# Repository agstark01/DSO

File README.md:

# DSO
Making a digital oscilloscope for frequency range upto 500khz and voltage range upto +-10V. Sharing the waveforms via pc communication to project it on gui using USB2.0 1MBps speed
## You can see full schematics in [DSO_1draft.pdf](assessment1/DSO_1draft/DSO_1draft.pdf).

## Hardware Subsystems & Circuit Schematics

### 1. Analog Input & Channel Multiplexing
Routes and selects between analog input channels and attenuation paths to direct the conditioned signal toward the sampling stage.

---

### 2. Anti-Aliasing Filter
An active low-pass filter stage designed to attenuate high-frequency components above the Nyquist limit, preventing aliasing distortion at the ADC inputs.

---

### 3. PWM-to-DC Offset Generator
Filters a high-frequency PWM signal from the microcontroller through a low-pass network, producing an adjustable analog DC offset to center and bias bipolar input waveforms within the ADC's 0–3.3V dynamic range.

---

### 4. Symmetric Dual Supply Generation (±5V)
Generates clean positive (this stage is updated please see pdf) (+5V) and negative (-5V) rails to supply the operational amplifiers, providing the necessary headroom and swing for true bipolar signal conditioning.

---

### 5. Onboard Function Generator
Generates test signals (e.g., standard 1 kHz square reference or calibration waveforms) for probe compensation, debugging, and self-testing.

---

### 6. Input Connectors & Channels
Interface connectors (BNC/header pins) for Channel 1 and Channel 2, providing signal entry, grounding, and initial protection.

---

### 7. MCU Programming & Debug Header
Breakout interface (SWD/JTAG and UART/power pins) for flashing firmware to the microcontroller and monitoring real-time telemetry during development.

---

### 8. Net Name & Pin Matching Guide
Reference diagram mapping schematic netlabels, board bus connections, and microcontroller GPIO pinouts across different modules.

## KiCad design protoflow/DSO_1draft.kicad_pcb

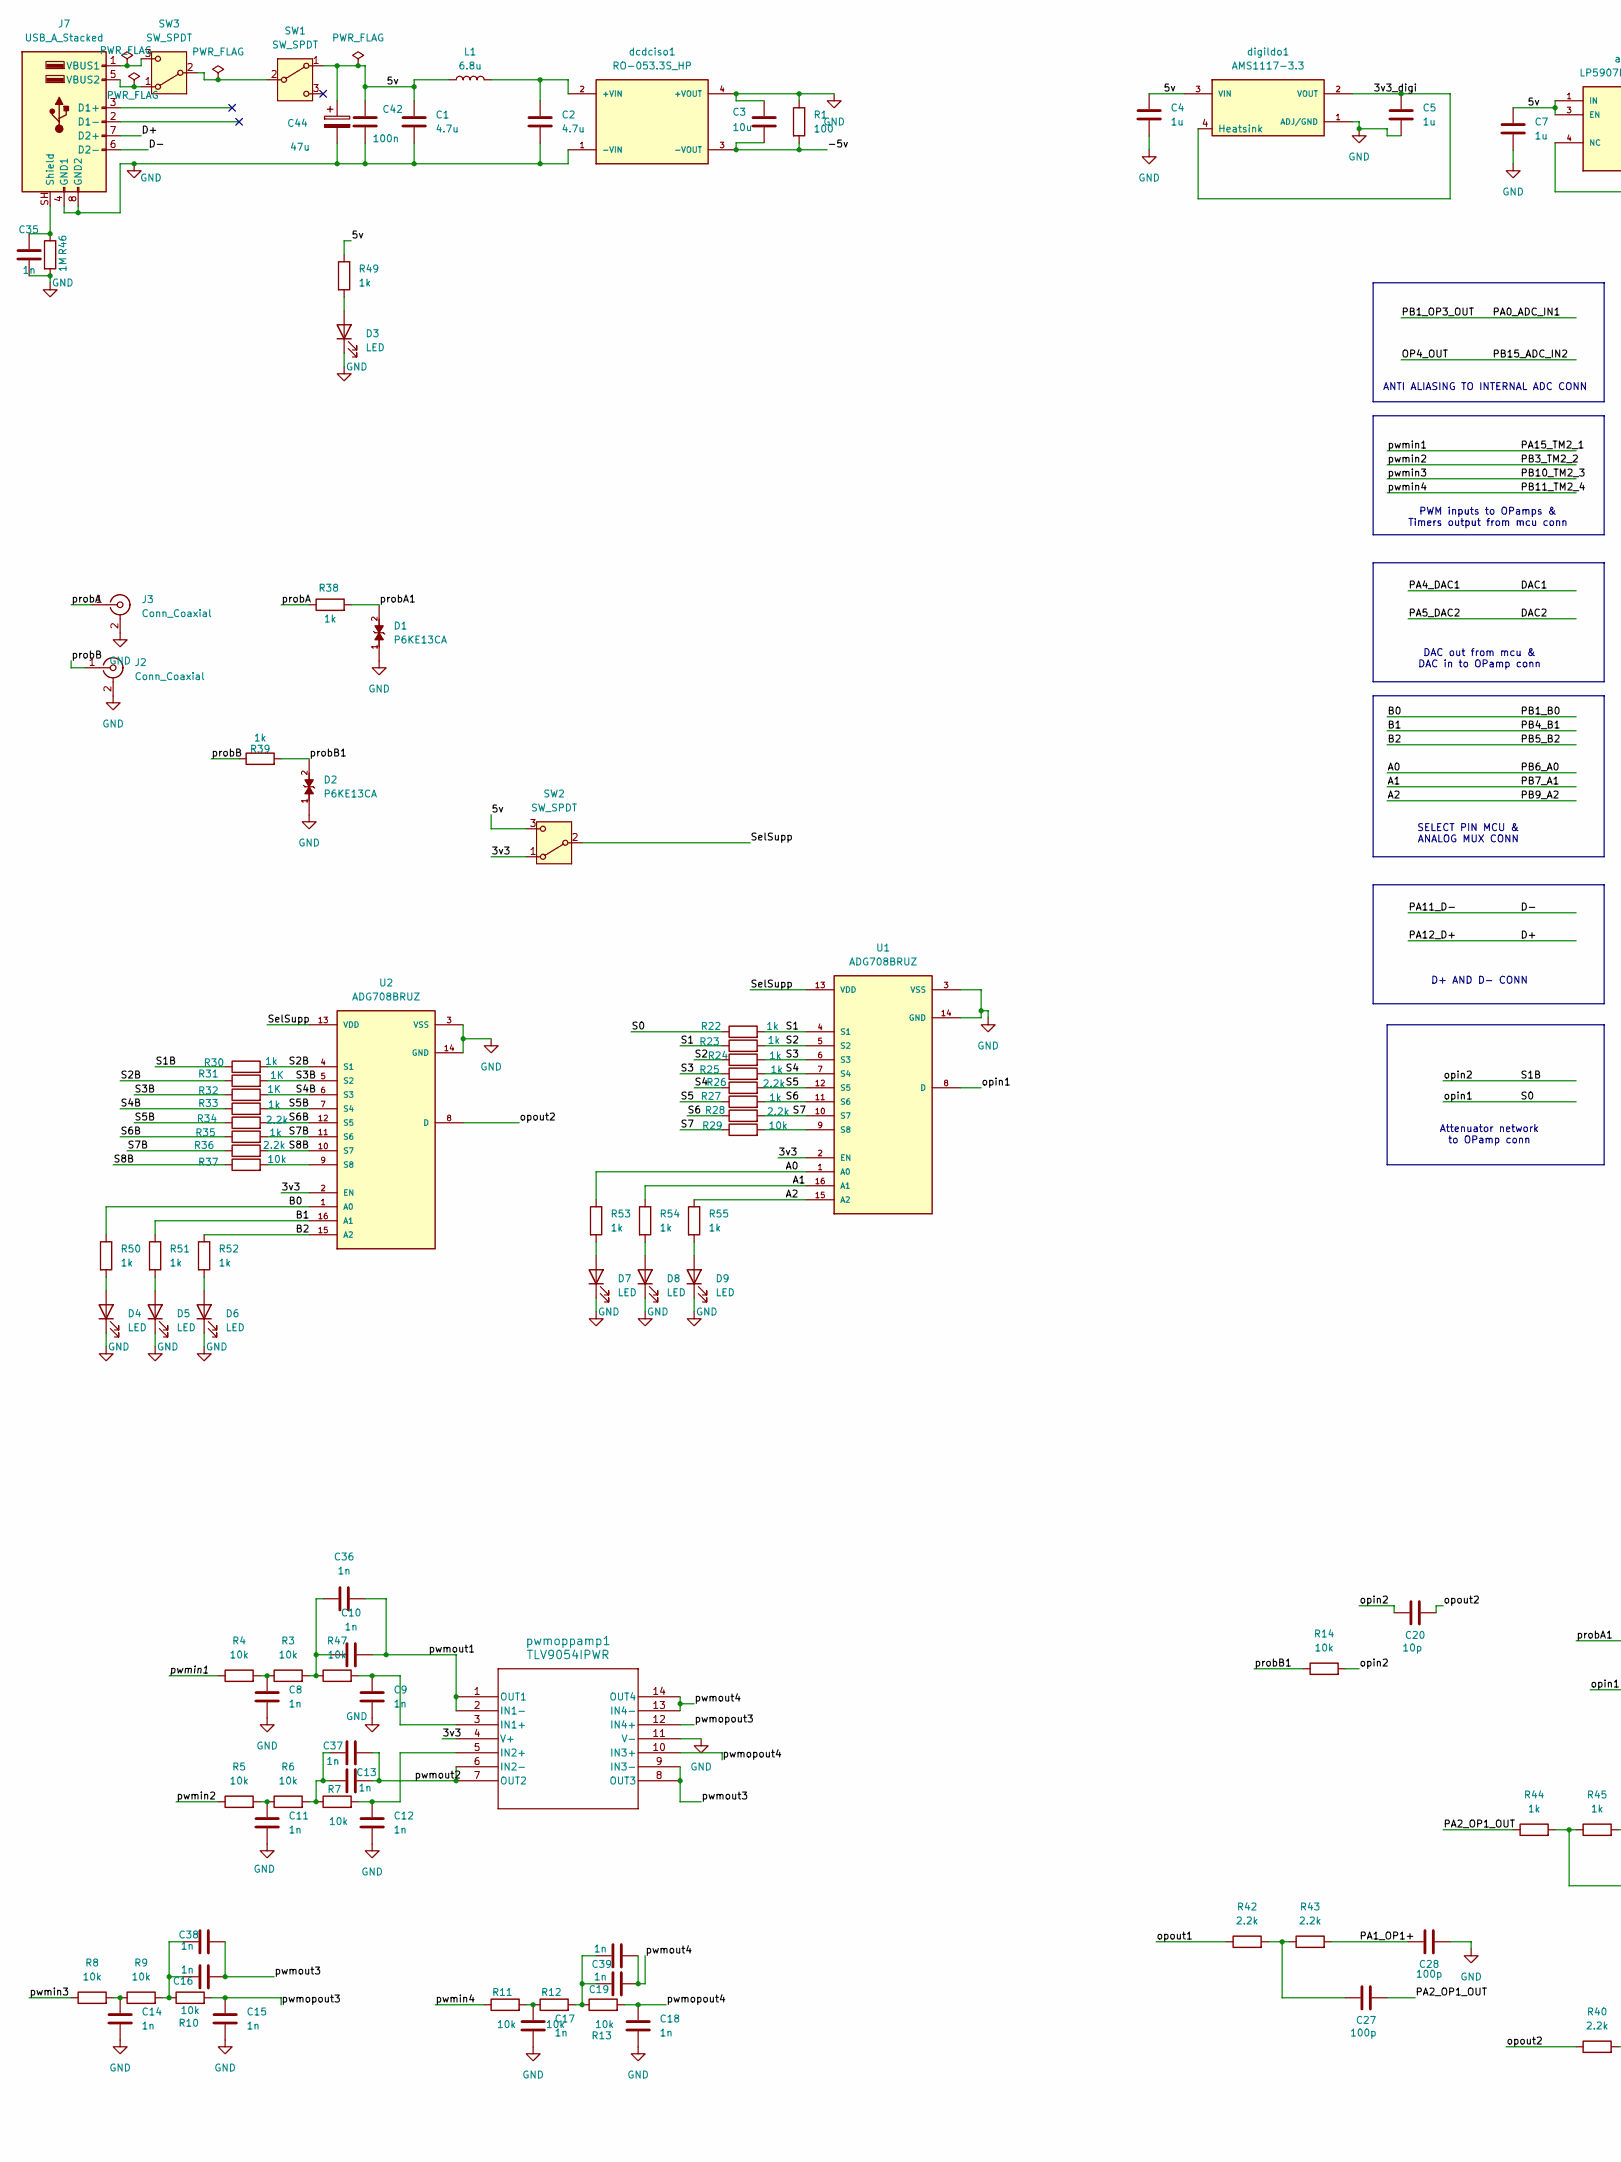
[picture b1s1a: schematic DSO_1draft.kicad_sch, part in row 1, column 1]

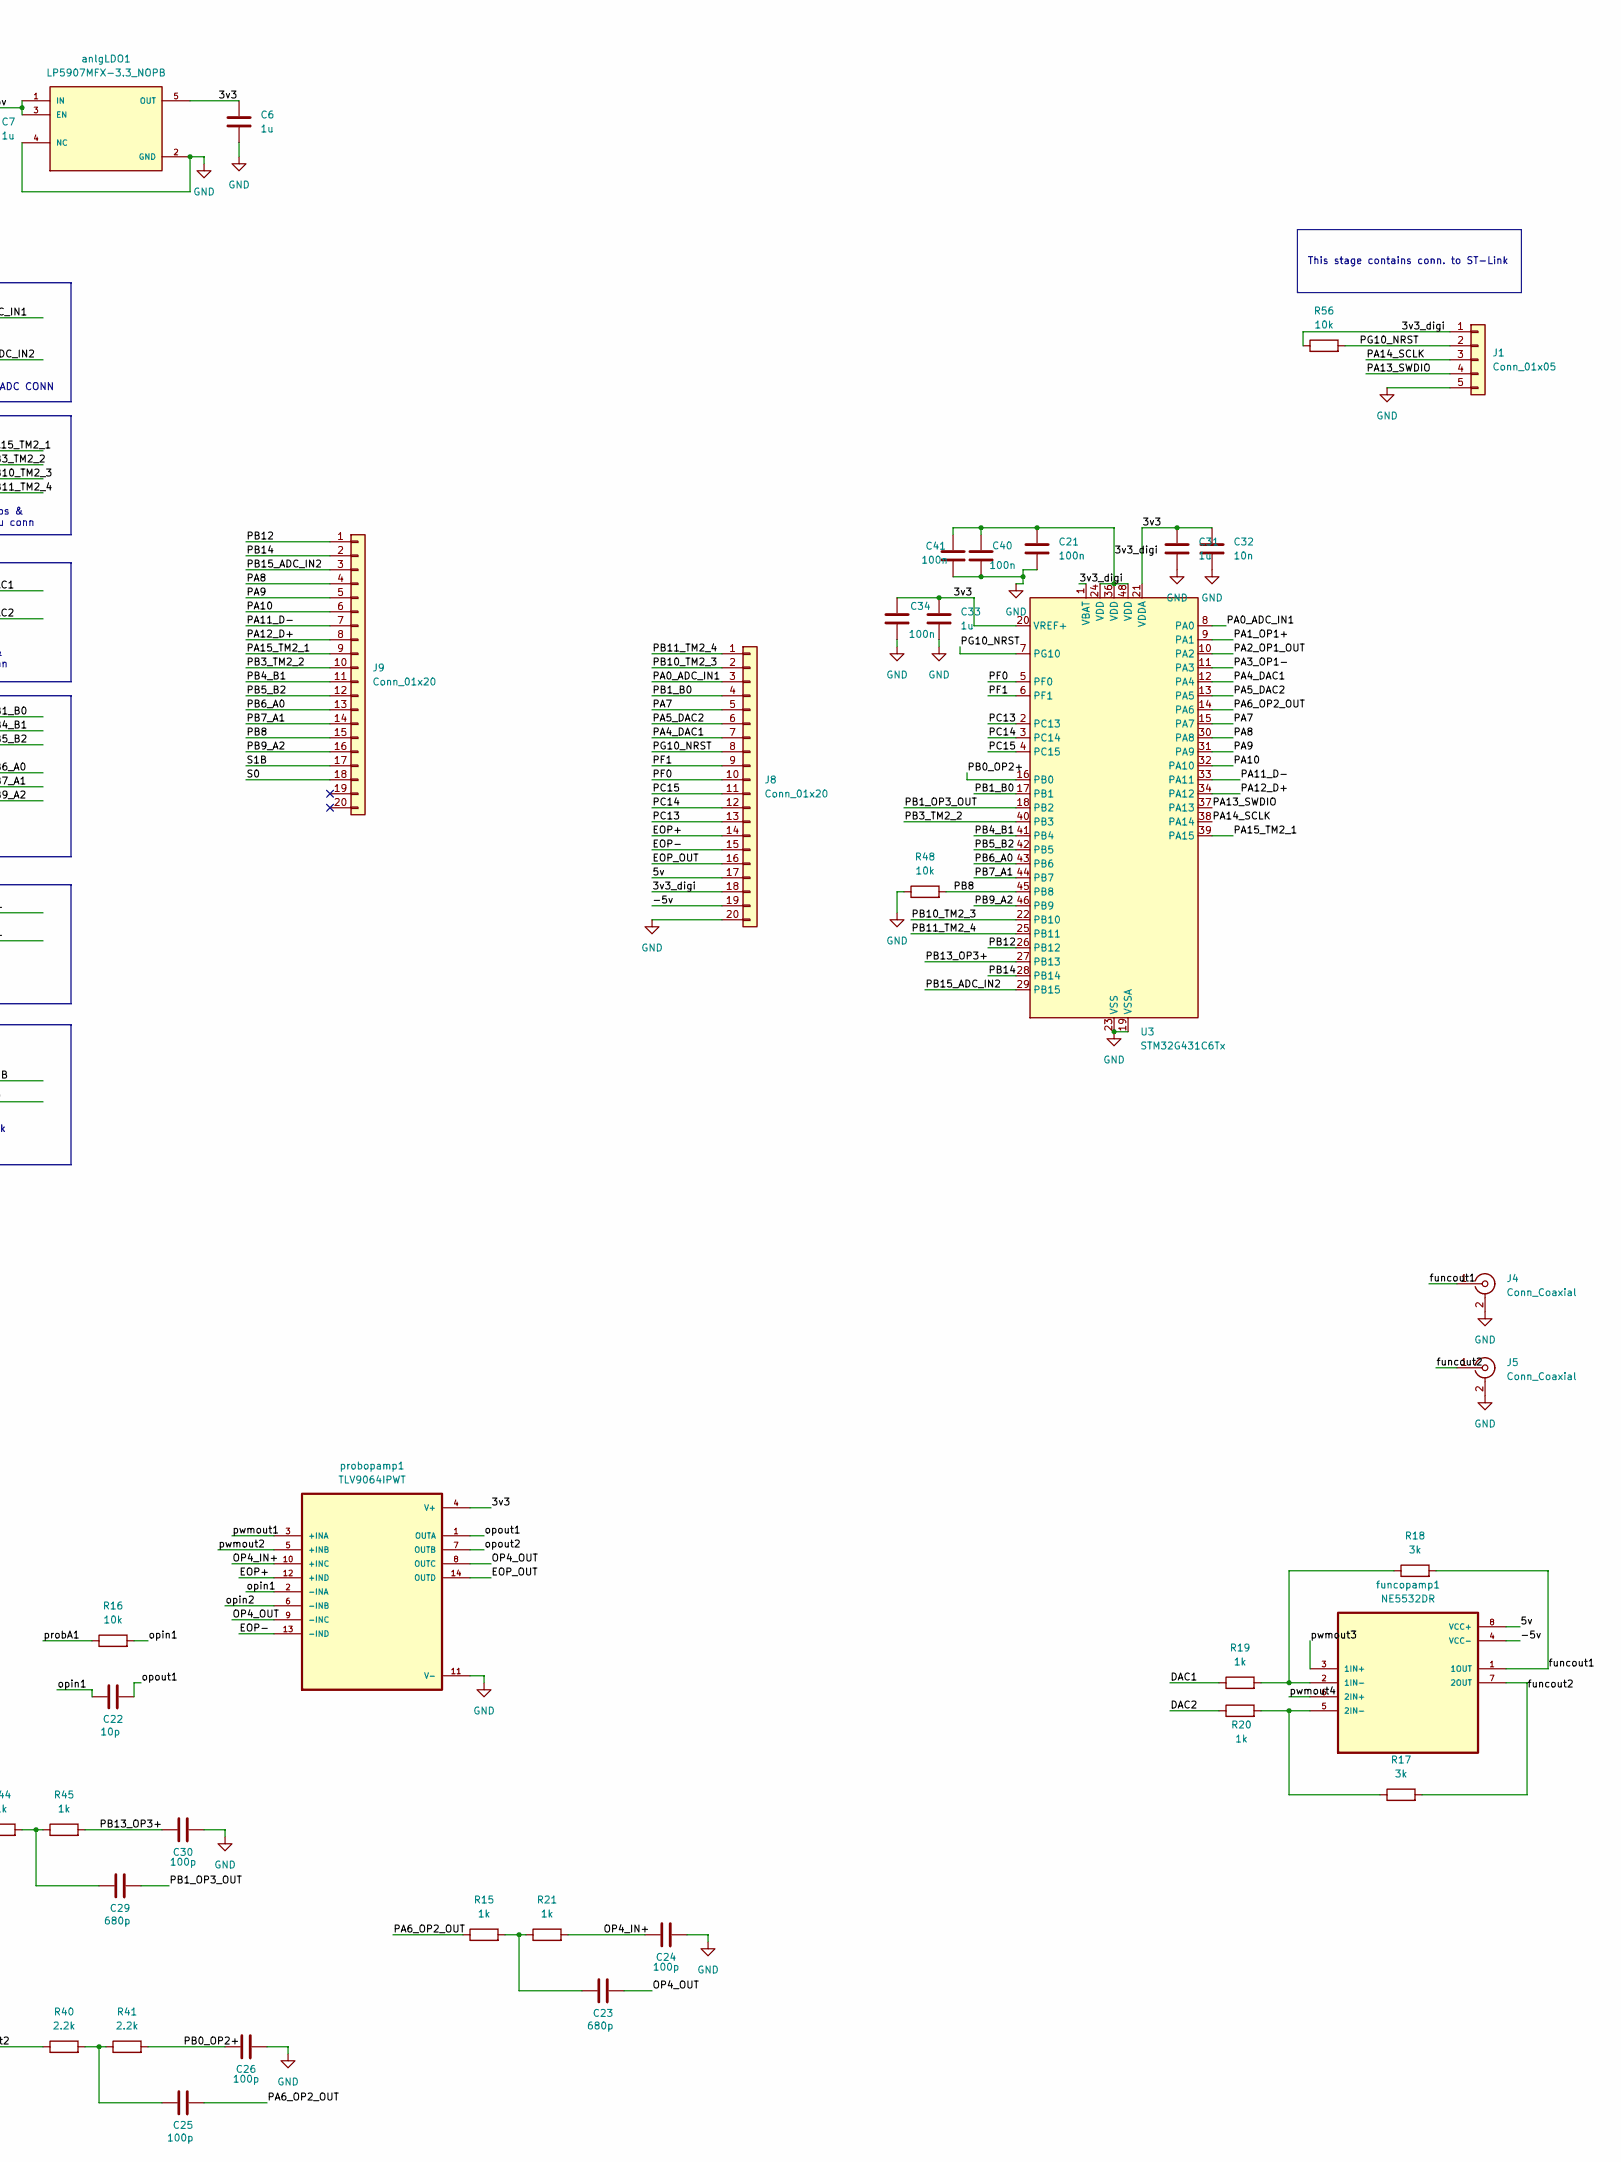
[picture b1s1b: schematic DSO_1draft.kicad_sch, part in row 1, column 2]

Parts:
C1, C2: 4.7u; C_1206_3216Metric_Pad1.33x1.80mm_HandSolder
C3: 10u; C_1206_3216Metric_Pad1.33x1.80mm_HandSolder
C4, C5, C6, C7, C31, C33: 1u; C_1206_3216Metric_Pad1.33x1.80mm_HandSolder
C8, C9, C10, C11, C12, C13, C14, C15, C16, C17, C18, C19, C35, C36, C37, C38, C39: 1n; C_1206_3216Metric_Pad1.33x1.80mm_HandSolder
C20, C22: 10p; C_1206_3216Metric_Pad1.33x1.80mm_HandSolder
C21, C34, C40, C41, C42: 100n; C_1206_3216Metric_Pad1.33x1.80mm_HandSolder
C23, C29: 680p; C_1206_3216Metric_Pad1.33x1.80mm_HandSolder
C24, C25, C26, C27, C28, C30: 100p; C_1206_3216Metric_Pad1.33x1.80mm_HandSolder
C32: 10n; C_1206_3216Metric_Pad1.33x1.80mm_HandSolder
C44: 47u; C_Radial_D5.0mm_H11.0mm_P2.00mm
D1, D2: P6KE13CA; DIOAD1300W80L670D310; PARTREV O2109
D3, D4, D5, D6, D7, D8, D9: LED; LED_1206_3216Metric
J1: Conn_01x05; PinHeader_1x05_P2.54mm_Vertical
J2, J3, J4, J5: Conn_Coaxial; BNC_Amphenol_B6252HB-NPP3G-50_Horizontal
J7: USB_A_Stacked; USB_A_CUI_UJ2-ADH-TH_Horizontal_Stacked
J8, J9: Conn_01x20; PinHeader_2x10_P2.54mm_Vertical
L1: 6.8u; L_Axial_L11.0mm_D4.5mm_P15.24mm_Horizontal_Fastron_MECC
R1: 100; R_Axial_DIN0207_L6.3mm_D2.5mm_P7.62mm_Horizontal
R3, R4, R5, R6, R7, R8, R9, R10, R11, R12, R13, R14, R16, R29, R37, R47, R48, R56: 10k; R_1206_3216Metric_Pad1.30x1.75mm_HandSolder
R15, R19, R20, R21, R22, R23, R24, R25, R27, R30, R33, R35, R38, R39, R44, R45, R49, R50, R51, R52, R53, R54, R55: 1k; R_1206_3216Metric_Pad1.30x1.75mm_HandSolder
R17, R18: 3k; R_1206_3216Metric_Pad1.30x1.75mm_HandSolder
R26, R28, R34, R36, R40, R41, R42, R43: 2.2k; R_1206_3216Metric_Pad1.30x1.75mm_HandSolder
R31, R32: 1K; R_1206_3216Metric_Pad1.30x1.75mm_HandSolder
R46: 1M; R_Axial_DIN0207_L6.3mm_D2.5mm_P7.62mm_Horizontal
SW1, SW2, SW3: SW_SPDT; SS-12F17_1P2T
U1, U2: ADG708BRUZ; TSSOP16
U3: STM32G431C6Tx; LQFP-48_7x7mm_P0.5mm
anlgLDO1: LP5907MFX-3.3_NOPB; SOT95P280X145-5N; PARTREV Q
dcdciso1: RO-053.3S_HP; CONV_RO-053.3S_HP; PARTREV 3
digildo1: AMS1117-3.3; SOT229P700X180-4N; PARTREV NA
funcopamp1: NE5532DR; SOIC127P599X175-8N
probopamp1: TLV9064IPWT; SOP65P640X120-14N
pwmoppamp1: TLV9054IPWR; U_TSSOP_PW_TEX-M

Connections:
/3v3: C6.1, C31.1, C32.1, C33.1, C34.1, SW2.1 (A), U1.2 (EN), U2.2 (EN), U3.20 (VREF+), U3.21 (VDDA), anlgLDO1.5 (OUT), probopamp1.4 (V+), pwmoppamp1.4 (V+)
/3v3_digi: C5.1, C21.1, C40.1, C41.1, J1.1, J8.18, R56.1, U3.1 (VBAT), U3.24 (VDD), U3.36 (VDD), U3.48 (VDD), digildo1.2 (VOUT), digildo1.4 (Heatsink)
/5v: C1.1, C4.1, C7.1, C42.1, C44.1, J8.17, L1.1, R49.1, SW1.1 (A), SW2.3 (C), anlgLDO1.1 (IN), anlgLDO1.3 (EN), digildo1.3 (VIN), funcopamp1.8 (VCC+)
/-5v: C3.2, J8.19, R1.2, dcdciso1.3 (-VOUT), funcopamp1.4 (VCC-)
/A0: J9.13, R53.1, U1.1 (A0), U3.43 (PB6)
/A1: J9.14, R54.1, U1.16 (A1), U3.44 (PB7)
/A2: J9.16, R55.1, U1.15 (A2), U3.46 (PB9)
/B0: J8.4, R50.1, U2.1 (A0), U3.17 (PB1)
/B1: J9.11, R51.1, U2.16 (A1), U3.41 (PB4)
/B2: J9.12, R52.1, U2.15 (A2), U3.42 (PB5)
/D+: J7.7 (D2+), J9.8, U3.34 (PA12)
/D-: J7.6 (D2-), J9.7, U3.33 (PA11)
/DAC1: J8.7, R19.1, U3.12 (PA4)
/DAC2: J8.6, R20.1, U3.13 (PA5)
/EOP+: J8.14, probopamp1.12 (+IND)
/EOP-: J8.15, probopamp1.13 (-IND)
/EOP_OUT: J8.16, probopamp1.14 (OUTD)
/OP4_IN+: C24.1, R21.2, probopamp1.10 (+INC)
/OP4_OUT: C23.2, J9.3, U3.29 (PB15), probopamp1.8 (OUTC), probopamp1.9 (-INC)
/PA0_ADC_IN1: C29.2, J8.3, U3.8 (PA0), U3.18 (PB2)
/PA1_OP1+: C28.1, R43.2, U3.9 (PA1)
/PA2_OP1_OUT: C27.2, R44.1, U3.10 (PA2)
/PA3_OP1-: U3.11 (PA3)
/PA6_OP2_OUT: C25.2, R15.1, U3.14 (PA6)
/PA7: J8.5, U3.15 (PA7)
/PA8: J9.4, U3.30 (PA8)
/PA9: J9.5, U3.31 (PA9)
/PA10: J9.6, U3.32 (PA10)
/PA13_SWDIO: J1.4, U3.37 (PA13)
/PA14_SCLK: J1.3, U3.38 (PA14)
/PA15_TM2_1: J9.9, R4.1, U3.39 (PA15)
/PB0_OP2+: C26.1, R41.2, U3.16 (PB0)
/PB3_TM2_2: J9.10, R5.1, U3.40 (PB3)
/PB8: J9.15, R48.2, U3.45 (PB8)
/PB10_TM2_3: J8.2, R8.1, U3.22 (PB10)
/PB11_TM2_4: J8.1, R11.1, U3.25 (PB11)
/PB12: J9.1, U3.26 (PB12)
/PB13_OP3+: C30.1, R45.2, U3.27 (PB13)
/PB14: J9.2, U3.28 (PB14)
/PC13: J8.13, U3.2 (PC13)
/PC14: J8.12, U3.3 (PC14)
/PC15: J8.11, U3.4 (PC15)
/PF0: J8.10, U3.5 (PF0)
/PF1: J8.9, U3.6 (PF1)
/PG10_NRST: J1.2, J8.8, R56.2, U3.7 (PG10)
/S0: C22.1, J9.18, R16.2, R22.1, U1.8 (D), probopamp1.2 (-INA)
/S1: R22.2, R23.1, U1.4 (S1)
/S1B: C20.1, J9.17, R14.2, R30.1, probopamp1.6 (-INB)
/S2: R23.2, R24.1, U1.5 (S2)
/S2B: R30.2, R31.1, U2.4 (S1)
/S3: R24.2, R25.1, U1.6 (S3)
/S3B: R31.2, R32.1, U2.5 (S2)
/S4: R25.2, R26.1, U1.7 (S4)
/S4B: R32.2, R33.1, U2.6 (S3)
/S5: R26.2, R27.1, U1.12 (S5)
/S5B: R33.2, R34.1, U2.7 (S4)
/S6: R27.2, R28.1, U1.11 (S6)
/S6B: R34.2, R35.1, U2.12 (S5)
/S7: R28.2, R29.1, U1.10 (S7)
/S7B: R35.2, R36.1, U2.11 (S6)
/S8B: R36.2, R37.1, U2.10 (S7)
/SelSupp: SW2.2 (B), U1.13 (VDD), U2.13 (VDD)
/funcout1: J4.1 (In), R18.2, funcopamp1.1 (1OUT)
/funcout2: J5.1 (In), R17.2, funcopamp1.7 (2OUT)
/opout1: C22.2, R42.1, probopamp1.1 (OUTA)
/opout2: C20.2, R40.1, U2.8 (D), probopamp1.7 (OUTB)
/probA: J3.1 (In), R38.1
/probA1: D1.2, R16.1, R38.2
/probB: J2.1 (In), R39.1
/probB1: D2.2, R14.1, R39.2
/pwmopout3: C15.1, R10.2, pwmoppamp1.12 (IN4+)
/pwmopout4: C18.1, R13.2, pwmoppamp1.10 (IN3+)
/pwmout1: C10.2, C36.2, probopamp1.3 (+INA), pwmoppamp1.1 (OUT1), pwmoppamp1.2 (IN1-)
/pwmout2: C13.2, C37.2, probopamp1.5 (+INB), pwmoppamp1.6 (IN2-), pwmoppamp1.7 (OUT2)
/pwmout3: C16.2, C38.2, funcopamp1.3 (1IN+), pwmoppamp1.8 (OUT3), pwmoppamp1.9 (IN3-)
/pwmout4: C19.2, C39.2, funcopamp1.6 (2IN+), pwmoppamp1.13 (IN4-), pwmoppamp1.14 (OUT4)
GND: C1.2, C2.2, C3.1, C4.2, C5.2, C6.2, C7.2, C8.2, C9.2, C11.2, C12.2, C14.2, C15.2, C17.2, C18.2, C21.2, C24.2, C26.2, C28.2, C30.2, C31.2, C32.2, C33.2, C34.2, C35.2, C40.2, C41.2, C42.2, C44.2, D1.1, D2.1, D3.1 (K), D4.1 (K), D5.1 (K), D6.1 (K), D7.1 (K), D8.1 (K), D9.1 (K), J1.5, J2.2 (Ext), J3.2 (Ext), J4.2 (Ext), J5.2 (Ext), J7.4 (GND1), J7.8 (GND2), J8.20, R1.1, R46.2, R48.1, U1.3 (VSS), U1.14 (GND), U2.3 (VSS), U2.14 (GND), U3.19 (VSSA), U3.23 (VSS), U3.35 (VSS), U3.47 (VSS), anlgLDO1.2 (GND), anlgLDO1.4 (NC), dcdciso1.1 (-VIN), dcdciso1.4 (+VOUT), digildo1.1 (ADJ/GND), probopamp1.11 (V-), pwmoppamp1.11 (V-)
unnamed: C8.1, R3.1, R4.2
unnamed: C10.1, C36.1, R3.2, R47.1
unnamed: C11.1, R5.2, R6.1
unnamed: C13.1, C37.1, R6.2, R7.1
unnamed: C14.1, R8.2, R9.1
unnamed: C16.1, C38.1, R9.2, R10.1
unnamed: C17.1, R11.2, R12.1
unnamed: C19.1, C39.1, R12.2, R13.1
unnamed: C23.1, R15.2, R21.1
unnamed: C25.1, R40.2, R41.1
unnamed: C27.1, R42.2, R43.1
unnamed: C29.1, R44.2, R45.1
unnamed: D3.2 (A), R49.2
unnamed: D4.2 (A), R50.2
unnamed: D5.2 (A), R51.2
unnamed: D6.2 (A), R52.2
unnamed: D7.2 (A), R53.2
unnamed: D8.2 (A), R54.2
unnamed: D9.2 (A), R55.2
unnamed: C35.1, J7.SH (Shield), R46.1
unnamed: J7.1 (VBUS1), SW3.3 (C)
unnamed: J7.5 (VBUS2), SW3.1 (A)
unnamed: SW1.2 (B), SW3.2 (B)
unnamed: R29.2, U1.9 (S8)
unnamed: R37.2, U2.9 (S8)
unnamed: C2.1, L1.2, dcdciso1.2 (+VIN)
unnamed: R18.1, R19.2, funcopamp1.2 (1IN-)
unnamed: R17.1, R20.2, funcopamp1.5 (2IN-)
unnamed: C9.1, R47.2, pwmoppamp1.3 (IN1+)
unnamed: C12.1, R7.2, pwmoppamp1.5 (IN2+)

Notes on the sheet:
Attenuator network to OPamp conn
SELECT PIN MCU & ANALOG MUX CONN
ANTI ALIASING TO INTERNAL ADC CONN
DAC out from mcu & DAC in to OPamp conn
This stage contains conn. to ST-Link
PWM inputs to OPamps & Timers output from mcu conn
D+ AND D- CONN

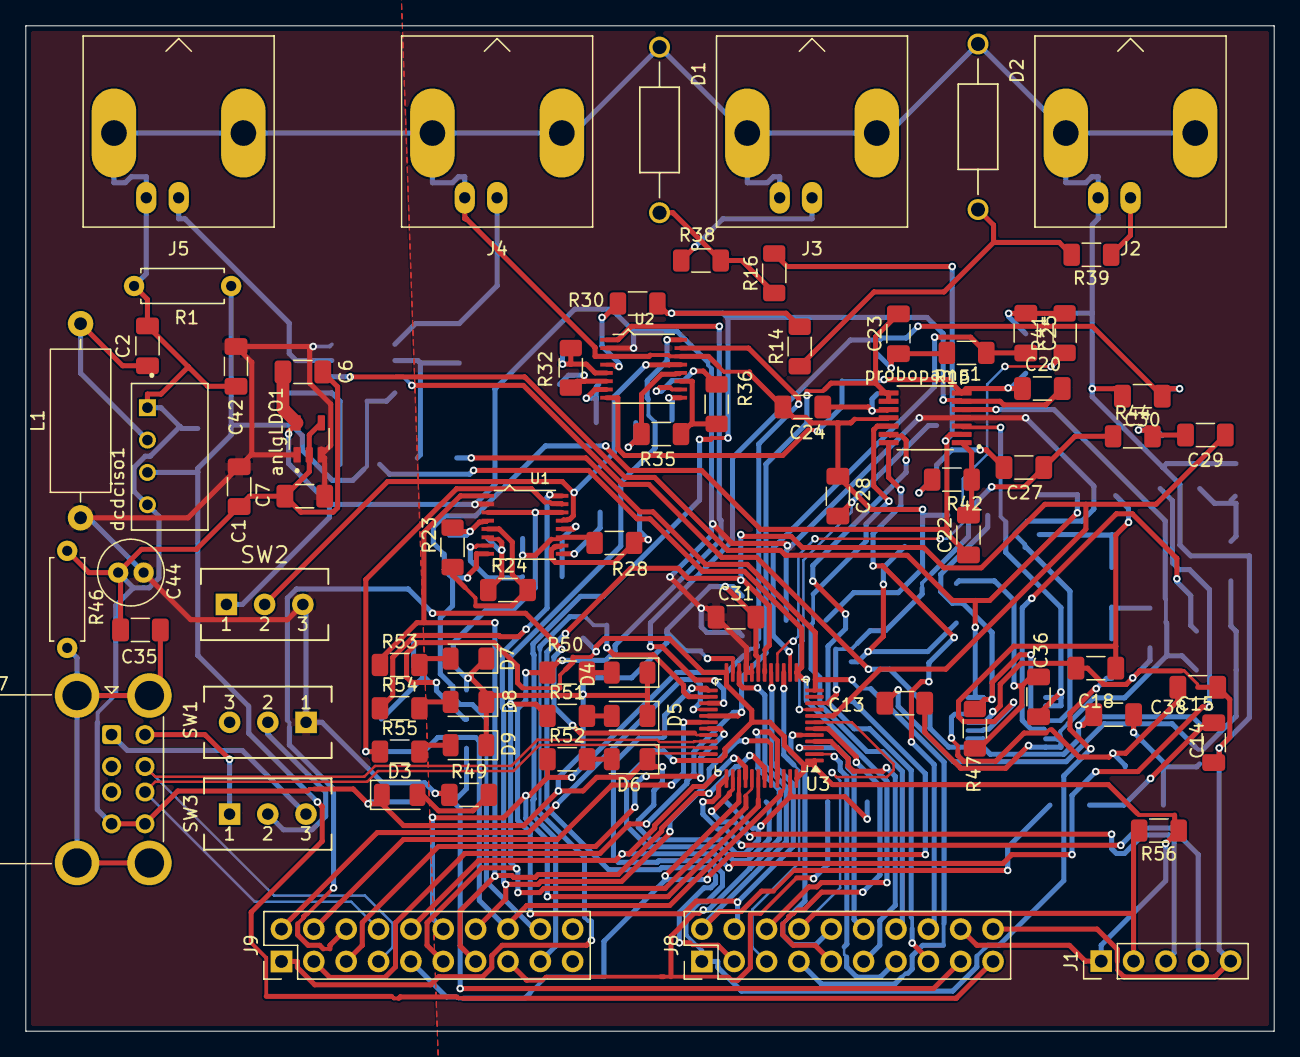
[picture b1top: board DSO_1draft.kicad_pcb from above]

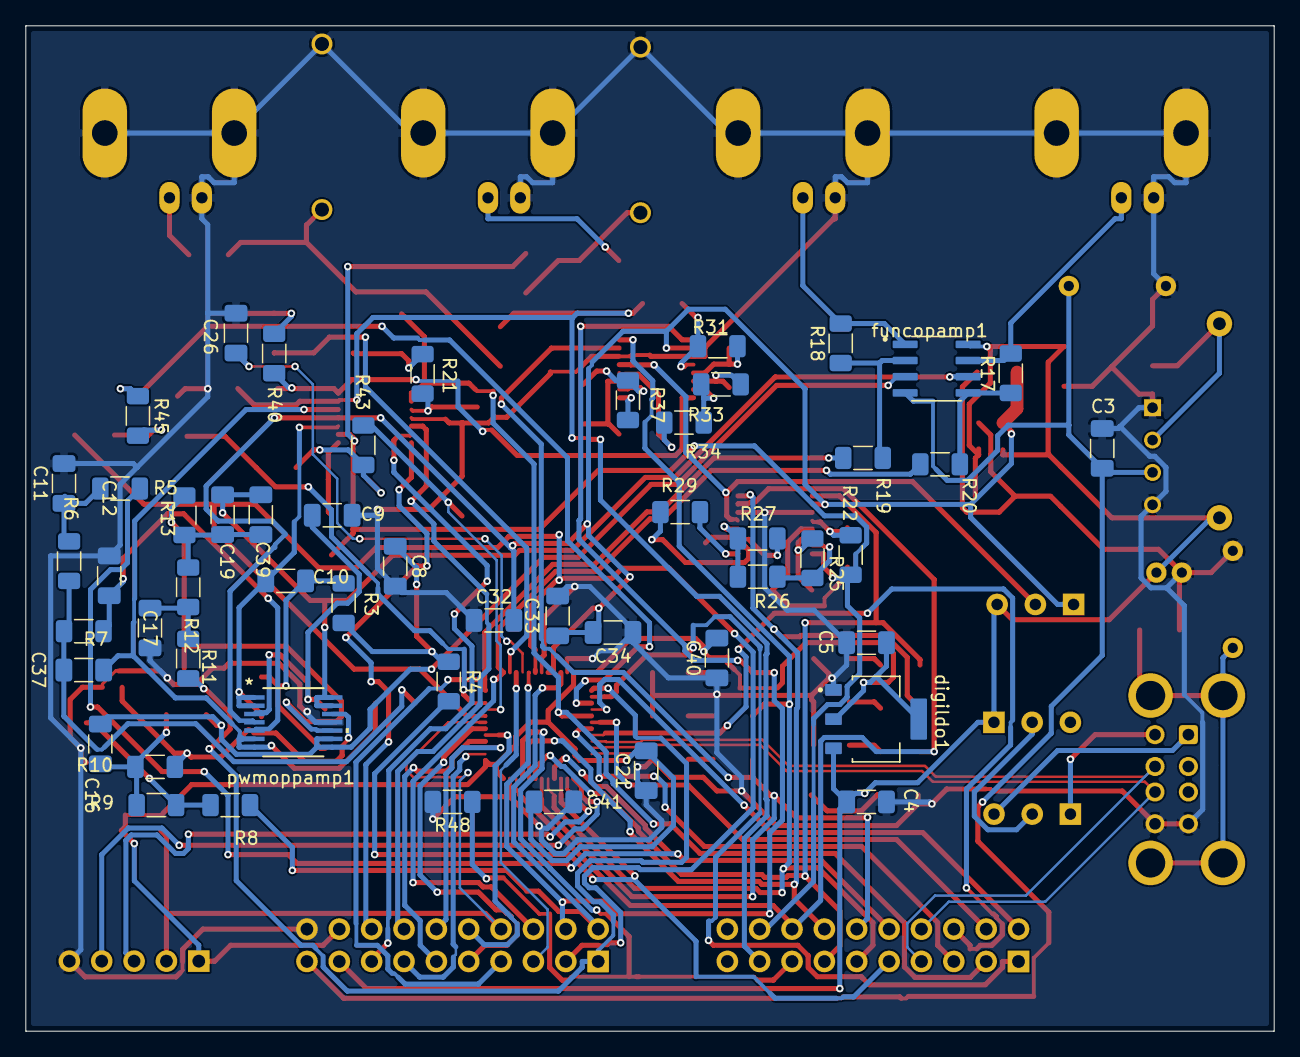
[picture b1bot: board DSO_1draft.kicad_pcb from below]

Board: 2 copper layers, 98.0 x 78.9 mm, 128 parts (52 on the bottom side), 106 nets.

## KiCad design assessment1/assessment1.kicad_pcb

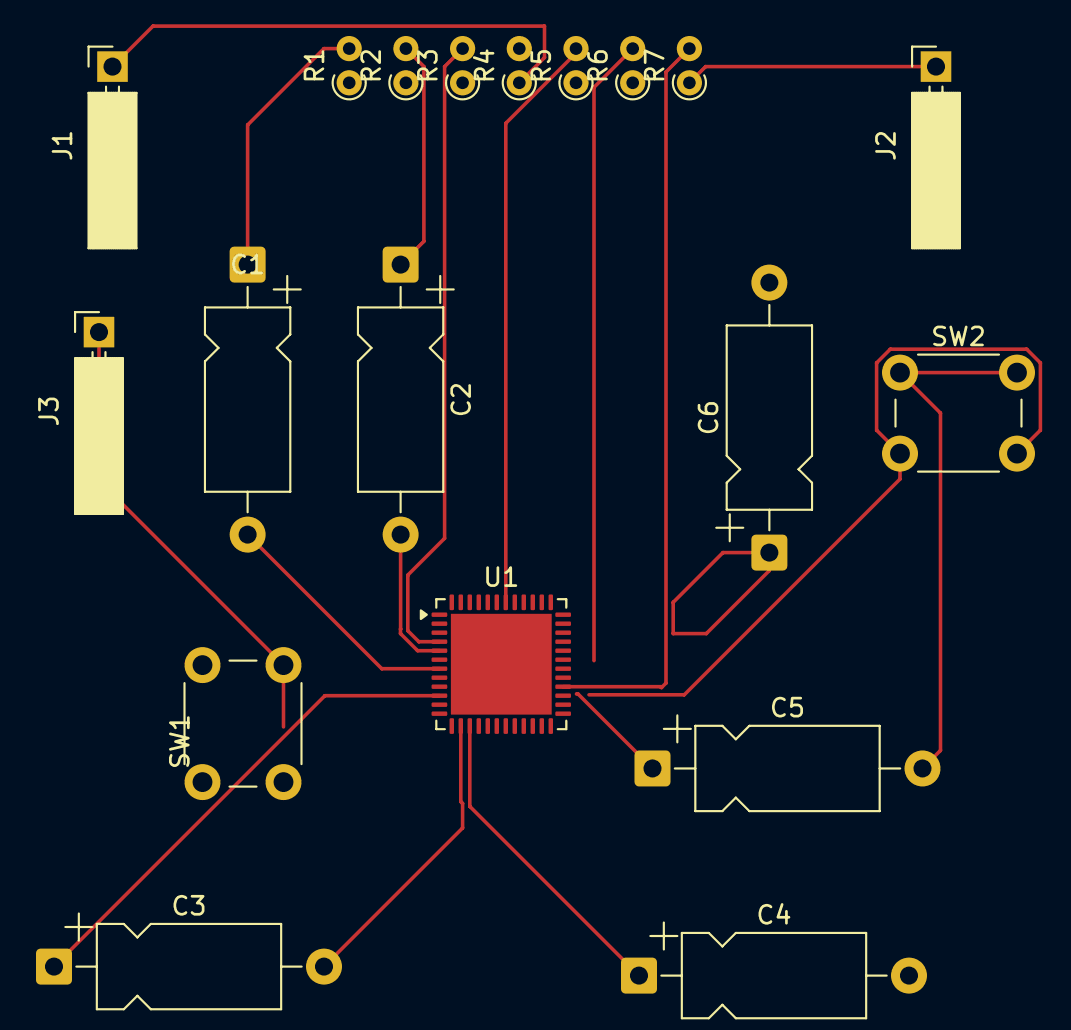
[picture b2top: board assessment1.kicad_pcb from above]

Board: 2 copper layers, 19 parts (0 on the bottom side), 20 nets.

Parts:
C1, C2, C3, C4, C5, C6: C; CP_Axial_L10.0mm_D4.5mm_P15.00mm_Horizontal
J1, J2, J3: Conn_01x04_Socket; PinSocket_1x01_P2.54mm_Horizontal
R1, R2, R3, R4, R5, R6, R7: R; R_Axial_DIN0204_L3.6mm_D1.6mm_P1.90mm_Vertical
SW1, SW2: SW_Push_Dual; SW_PUSH_6mm
U1: STM32F401CBUx; QFN-48-1EP_7x7mm_P0.5mm_EP5.6x5.6mm

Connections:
unnamed: C1.1, R1.2
unnamed: C2.1, R2.2
unnamed: C5.2, SW2.1
unnamed: J1.1 (Pin_1_1), R4.1
unnamed: J2.1 (Pin_1_1), R7.1
unnamed: J3.1 (Pin_1_1), SW1.2
unnamed: C1.2, U1.7 (NRST)
unnamed: C3.1, U1.10 (PA0)
unnamed: SW1.1, U1.11 (PA1)
unnamed: C3.2, U1.14 (PA4)
unnamed: C4.1, U1.15 (PA5)
unnamed: C5.1, U1.31 (PA10)
unnamed: SW2.2, U1.34 (PA13)
unnamed: C6.1, U1.38 (PA15)
unnamed: R4.2, U1.20 (PB2)
unnamed: R5.2, U1.42 (PB6)
unnamed: R6.2, U1.21 (PB10)
unnamed: R7.2, U1.28 (PB15)
unnamed: R3.2, U1.4 (PC15)
unnamed: C2.2, U1.5 (PH0)

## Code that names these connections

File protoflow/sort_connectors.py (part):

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
# 4. Exact J8 label replacements by coordinate & UUID (Pins 1..19 at X = 408.94)
J8_LABEL_UPDATES = [
    ('(label "PF0"\n\t\t(at 408.94 128.27 0)',       '(label "PB11_TM2_4"\n\t\t(at 408.94 128.27 0)'),
    ('(label "PF1"\n\t\t(at 408.94 130.81 0)',       '(label "PB10_TM2_3"\n\t\t(at 408.94 130.81 0)'),
    ('(label "PC13"\n\t\t(at 408.94 133.35 0)',      '(label "PA0_ADC_IN1"\n\t\t(at 408.94 133.35 0)'),
    ('(label "PC14"\n\t\t(at 408.94 135.89 0)',      '(label "PB1_B0"\n\t\t(at 408.94 135.89 0)'),
    ('(label "PC15"\n\t\t(at 408.94 138.43 0)',      '(label "PA7"\n\t\t(at 408.94 138.43 0)'),
    ('(label "PB12"\n\t\t(at 408.94 140.97 0)',      '(label "PA5_DAC2"\n\t\t(at 408.94 140.97 0)'),
    ('(label "PB14"\n\t\t(at 408.94 143.51 0)',      '(label "PA4_DAC1"\n\t\t(at 408.94 143.51 0)'),
    ('(label "PA7"\n\t\t(at 408.94 146.05 0)',       '(label "PG10_NRST"\n\t\t(at 408.94 146.05 0)'),
    ('(label "PA8"\n\t\t(at 408.94 148.59 0)',       '(label "PF1"\n\t\t(at 408.94 148.59 0)'),
    ('(label "PA9"\n\t\t(at 408.94 151.13 0)',       '(label "PF0"\n\t\t(at 408.94 151.13 0)'),
    ('(label "PA10"\n\t\t(at 408.94 153.67 0)',      '(label "PC15"\n\t\t(at 408.94 153.67 0)'),
    ('(label "EOP+"\n\t\t(at 408.94 156.21 0)',      '(label "PC14"\n\t\t(at 408.94 156.21 0)'),
    ('(label "EOP-"\n\t\t(at 408.94 158.75 0)',      '(label "PC13"\n\t\t(at 408.94 158.75 0)'),
    ('(label "EOP_OUT"\n\t\t(at 408.94 161.29 0)',   '(label "EOP+"\n\t\t(at 408.94 161.29 0)'),
    ('(label "PB8"\n\t\t(at 408.94 163.83 0)',       '(label "EOP-"\n\t\t(at 408.94 163.83 0)'),
    ('(label "PG10_NRST"\n\t\t(at 408.94 166.37 0)', '(label "EOP_OUT"\n\t\t(at 408.94 166.37 0)'),
]

# 5. New labels to place on J9's 18 wire stubs (Y = 107.95 to 151.13)
J9_NEW_LABELS = [
    (107.95, "PB12"),
    (110.49, "PB14"),
    (113.03, "PB15_ADC_IN2"),
    (115.57, "PA8"),
    (118.11, "PA9"),
    (120.65, "PA10"),
    (123.19, "PA11_D-"),
    (125.73, "PA12_D+"),
    (128.27, "PA15_TM2_1"),
    (130.81, "PB3_TM2_2"),
    (133.35, "PB4_B1"),
    (135.89, "PB5_B2"),
    (138.43, "PB6_A0"),
    (140.97, "PB7_A1"),
    (143.51, "PB8"),
    (146.05, "PB9_A2"),
    (148.59, "S1B"),
    (151.13, "S0"),
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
